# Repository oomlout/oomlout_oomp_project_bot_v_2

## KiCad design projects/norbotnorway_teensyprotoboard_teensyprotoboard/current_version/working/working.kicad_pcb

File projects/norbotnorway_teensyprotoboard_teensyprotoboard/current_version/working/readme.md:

# teensyprotoboard
 
## summary 
* id: norbotnorway_teensyprotoboard_teensyprotoboard
* user: norbotnorway
* name: teensyprotoboard
* board: teensyprotoboard
* repo: https://github.com/NorbotNorway/TeensyProtoboard
* src_file_repo_kicad_pcb: TeensyProtoboard.kicad_pcb
* src_file_repo_kicad_pcb_link: https://github.com/NorbotNorway/TeensyProtoboard/tree/master/TeensyProtoboard.kicad_pcb

* src_file_repo_sch: TeensyProtoboard.sch
* src_file_repo_sch_link: https://github.com/NorbotNorway/TeensyProtoboard/tree/master/TeensyProtoboard.sch
* full details link: https://github.com/oomlout/oomlout_oomp_project_bot_v_2/tree/main/projects/norbotnorway_teensyprotoboard_teensyprotoboard/current_version/working

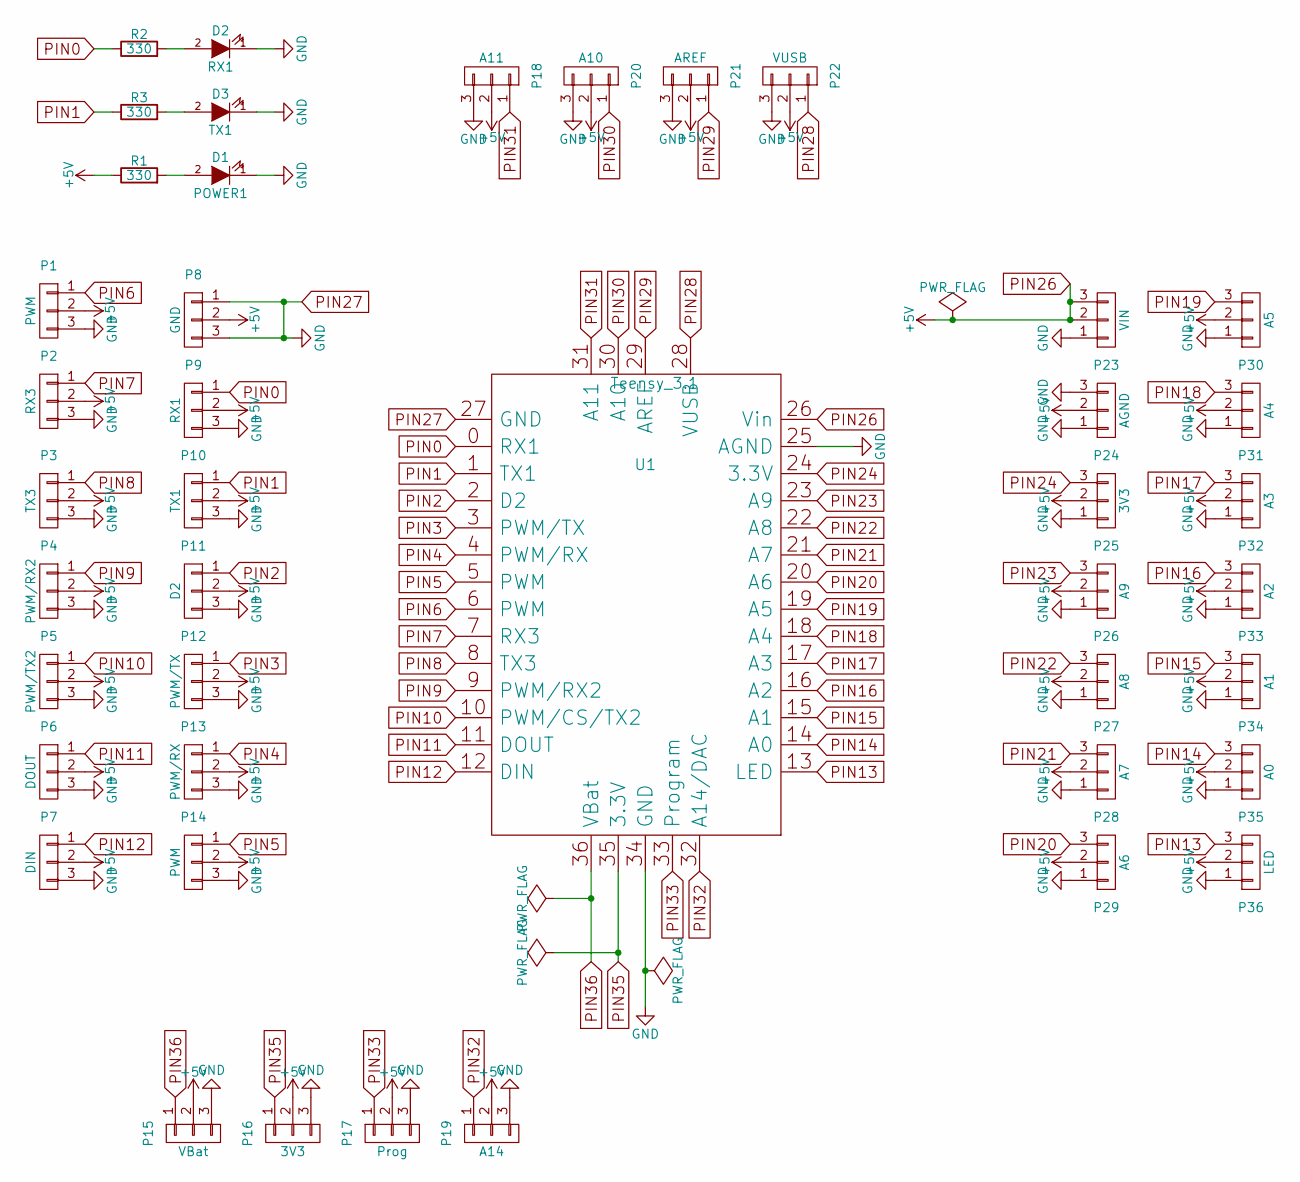
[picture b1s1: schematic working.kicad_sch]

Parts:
P1, P14: PWM; Pin_Header_Straight_1x03
P2: RX3; Pin_Header_Straight_1x03
P3: TX3; Pin_Header_Straight_1x03
P4: PWM/RX2; Pin_Header_Straight_1x03
P5: PWM/TX2; Pin_Header_Straight_1x03
P6: DOUT; Pin_Header_Straight_1x03
P7: DIN; Pin_Header_Straight_1x03
P8: GND; Pin_Header_Straight_1x03
P9: RX1; Pin_Header_Straight_1x03
P10: TX1; Pin_Header_Straight_1x03
P11: D2; Pin_Header_Straight_1x03
P12: PWM/TX; Pin_Header_Straight_1x03
P13: PWM/RX; Pin_Header_Straight_1x03
P15: VBat; Pin_Header_Straight_1x03
P16, P25: 3V3; Pin_Header_Straight_1x03
P17: Prog; Pin_Header_Straight_1x03
P18: A11; Pin_Header_Straight_1x03
P19: A14; Pin_Header_Straight_1x03
P20: A10; Pin_Header_Straight_1x03
P21: AREF; Pin_Header_Straight_1x03
P22: VUSB; Pin_Header_Straight_1x03
P23: VIN; Pin_Header_Straight_1x03
P24: AGND; Pin_Header_Straight_1x03
P26: A9; Pin_Header_Straight_1x03
P27: A8; Pin_Header_Straight_1x03
P28: A7; Pin_Header_Straight_1x03
P29: A6; Pin_Header_Straight_1x03
P30: A5; Pin_Header_Straight_1x03
P31: A4; Pin_Header_Straight_1x03
P32: A3; Pin_Header_Straight_1x03
P33: A2; Pin_Header_Straight_1x03
P34: A1; Pin_Header_Straight_1x03
P35: A0; Pin_Header_Straight_1x03
P36: LED; Pin_Header_Straight_1x03
POWER1: D1; SMB_Standard
R1, R2, R3: 330; R_0805_HandSoldering
RX1: D2; SMB_Standard
TX1: D3; SMB_Standard
U1: Teensy_3.1; Teensy-3.1_3.2

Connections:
unnamed: POWER1.2 (A), R1.2
unnamed: R2.2, RX1.2 (A)
unnamed: R3.2, TX1.2 (A)
PIN0: P9.1, R2.1, U1.0 (RX1)
PIN1: P10.1, R3.1, U1.1 (TX1)
PIN2: P11.1, U1.2 (D2)
PIN3: P12.1, U1.3 (PWM/TX)
PIN4: P13.1, U1.4 (PWM/RX)
PIN5: P14.1, U1.5 (PWM)
PIN6: P1.1, U1.6 (PWM)
PIN7: P2.1, U1.7 (RX3)
PIN8: P3.1, U1.8 (TX3)
PIN9: P4.1, U1.9 (PWM/RX2)
PIN10: P5.1, U1.10 (PWM/CS/TX2)
PIN11: P6.1, U1.11 (DOUT)
PIN12: P7.1, U1.12 (DIN)
PIN13: P36.3, U1.13 (LED)
PIN14: P35.3, U1.14 (A0)
PIN15: P34.3, U1.15 (A1)
PIN16: P33.3, U1.16 (A2)
PIN17: P32.3, U1.17 (A3)
PIN18: P31.3, U1.18 (A4)
PIN19: P30.3, U1.19 (A5)
PIN20: P29.3, U1.20 (A6)
PIN21: P28.3, U1.21 (A7)
PIN22: P27.3, U1.22 (A8)
PIN23: P26.3, U1.23 (A9)
PIN24: P25.3, U1.24 (3.3V)
PIN26: P1.2, P2.2, P3.2, P4.2, P5.2, P6.2, P7.2, P8.2, P9.2, P10.2, P11.2, P12.2, P13.2, P14.2, P15.2, P16.2, P17.2, P18.2, P19.2, P20.2, P21.2, P22.2, P23.2, P23.3, P24.2, P25.2, P26.2, P27.2, P28.2, P29.2, P30.2, P31.2, P32.2, P33.2, P34.2, P35.2, P36.2, R1.1, U1.26 (Vin)
PIN27: P1.3, P2.3, P3.3, P4.3, P5.3, P6.3, P7.3, P8.1, P8.3, P9.3, P10.3, P11.3, P12.3, P13.3, P14.3, P15.3, P16.3, P17.3, P18.3, P19.3, P20.3, P21.3, P22.3, P23.1, P24.1, P24.3, P25.1, P26.1, P27.1, P28.1, P29.1, P30.1, P31.1, P32.1, P33.1, P34.1, P35.1, P36.1, POWER1.1 (K), RX1.1 (K), TX1.1 (K), U1.25 (AGND), U1.27 (GND), U1.34 (GND)
PIN28: P22.1, U1.28 (VUSB)
PIN29: P21.1, U1.29 (AREF)
PIN30: P20.1, U1.30 (A10)
PIN31: P18.1, U1.31 (A11)
PIN32: P19.1, U1.32 (A14/DAC)
PIN33: P17.1, U1.33 (Program)
PIN35: P16.1, U1.35 (3.3V)
PIN36: P15.1, U1.36 (VBat)

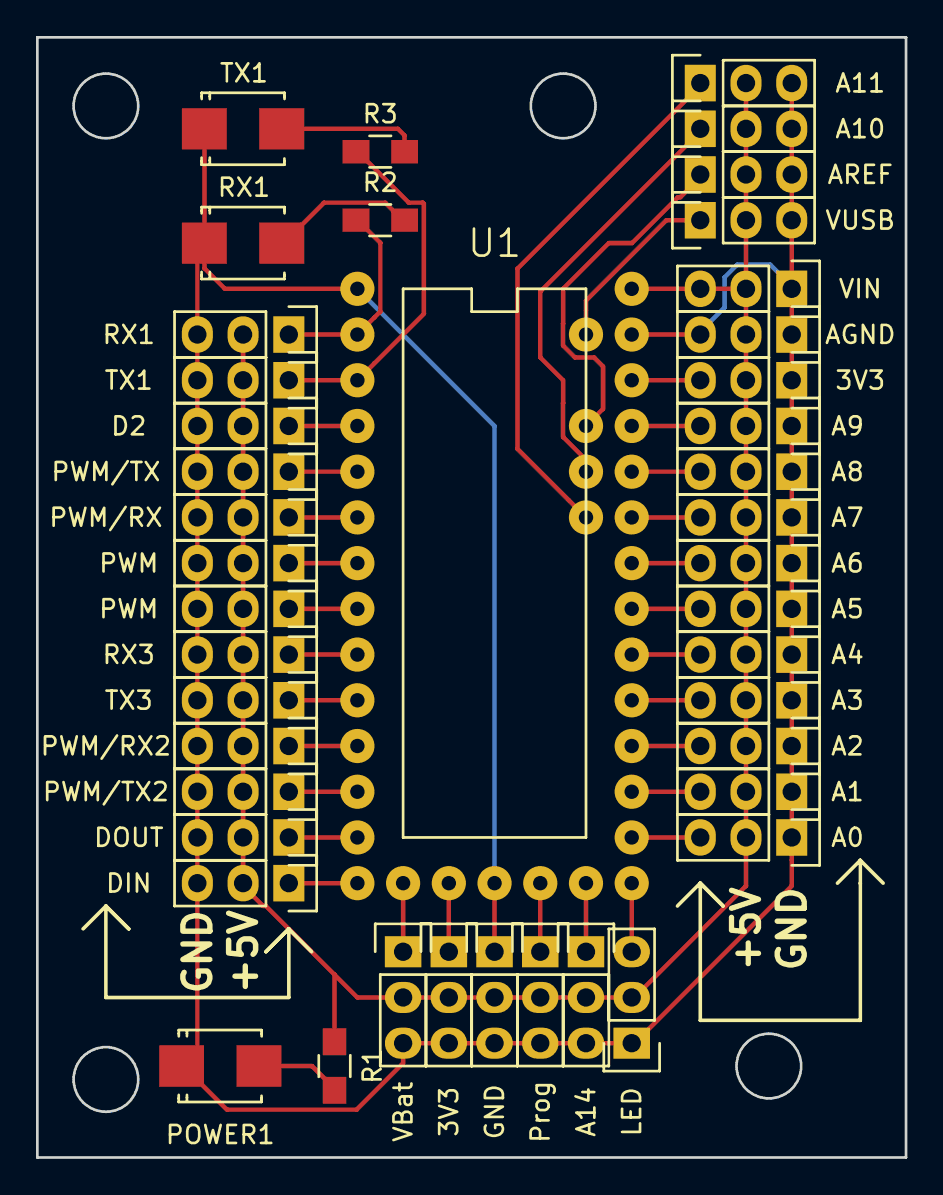
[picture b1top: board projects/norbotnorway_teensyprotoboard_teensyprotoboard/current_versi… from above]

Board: 2 copper layers, 48.3 x 62.2 mm, 43 parts (0 on the bottom side), 38 nets.

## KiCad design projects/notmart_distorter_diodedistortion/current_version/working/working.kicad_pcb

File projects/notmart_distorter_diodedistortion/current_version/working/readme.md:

# distorter
 
## summary 
* id: notmart_distorter_diodedistortion
* user: notmart
* name: distorter
* board: diodedistortion
* repo: https://github.com/notmart/distorter
* src_file_repo_kicad_pcb: diodedistortion.kicad_pcb
* src_file_repo_kicad_pcb_link: https://github.com/notmart/distorter/tree/master/diodedistortion.kicad_pcb

* src_file_repo_sch: diodedistortion.sch
* src_file_repo_sch_link: https://github.com/notmart/distorter/tree/master/diodedistortion.sch
* full details link: https://github.com/oomlout/oomlout_oomp_project_bot_v_2/tree/main/projects/notmart_distorter_diodedistortion/current_version/working

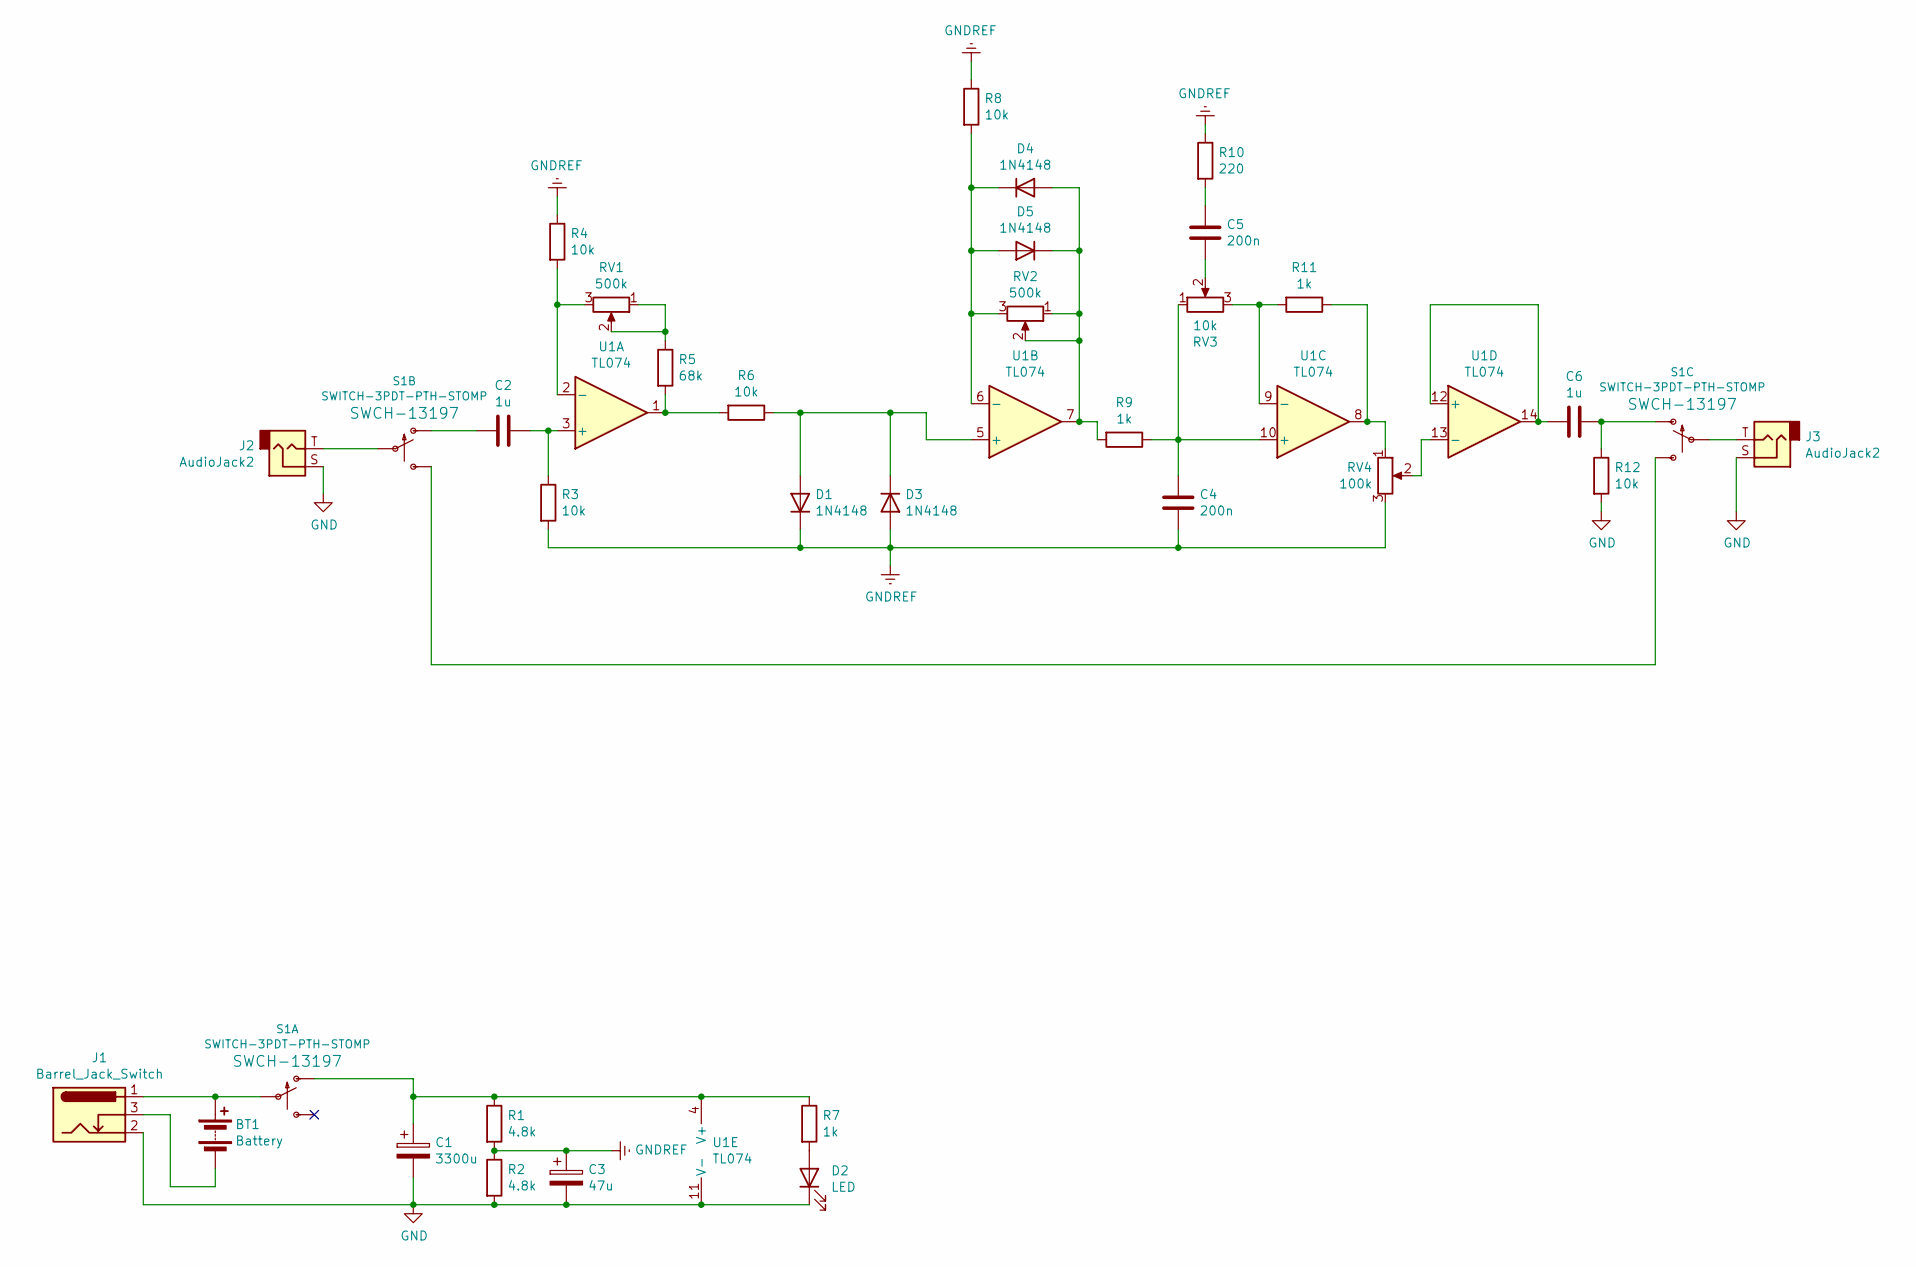
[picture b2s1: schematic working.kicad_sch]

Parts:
BT1: Battery; 1X02
C1: 3300u; CP_Radial_D13.0mm_P5.00mm
C2, C6: 1u; C_Rect_L7.2mm_W2.5mm_P5.00mm_FKS2_FKP2_MKS2_MKP2
C3: 47u; CP_Radial_D8.0mm_P5.00mm
C4, C5: 200n; C_Rect_L7.2mm_W2.5mm_P5.00mm_FKS2_FKP2_MKS2_MKP2
D1, D3, D4, D5: 1N4148; D_DO-35_SOD27_P7.62mm_Horizontal
D2: LED; LED_D3.0mm
J1: Barrel_Jack_Switch; BarrelJack_Horizontal
J2, J3: AudioJack2; Jack 6.35mm PJ603
R1, R2: 4.8k; R_Axial_DIN0204_L3.6mm_D1.6mm_P7.62mm_Horizontal
R3, R4, R6, R8, R12: 10k; R_Axial_DIN0204_L3.6mm_D1.6mm_P7.62mm_Horizontal
R5: 68k; R_Axial_DIN0204_L3.6mm_D1.6mm_P7.62mm_Horizontal
R7, R9, R11: 1k; R_Axial_DIN0204_L3.6mm_D1.6mm_P7.62mm_Horizontal
R10: 220; R_Axial_DIN0204_L3.6mm_D1.6mm_P7.62mm_Horizontal
RV1, RV2: 500k; Potentiometer_Alps_RK09K_Single_Vertical
RV3: 10k; Potentiometer_Alps_RK09K_Single_Vertical
RV4: 100k; Potentiometer_Bourns_3386P_Vertical
S1: SWITCH-3PDT-PTH-STOMP; 3PDT_Small
U1: TL074; DIP-14_W7.62mm_Socket_LongPads

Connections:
GND: C1.2, C3.2, D2.1 (K), J1.2, J2.S, J3.S, R2.2, R12.2, U1.11 (V-)
GNDREF: C3.1, C4.2, D1.1 (K), D3.2 (A), R1.2, R2.1, R3.2, R4.1, R8.1, R10.1, RV4.3
unnamed: BT1.1 (+), J1.1, S1.P$2
unnamed: BT1.2 (-), J1.3
unnamed: C1.1, R1.1, R7.1, S1.P$1 (O), U1.4 (V+)
unnamed: C2.1, R3.1, U1.3 (+)
unnamed: C2.2, S1.P$4 (O)
unnamed: C4.1, R9.1, RV3.1, U1.10 (+)
unnamed: C5.1, R10.2
unnamed: C5.2, RV3.2
unnamed: C6.1, R12.1, S1.P$7 (O)
unnamed: C6.2, U1.12 (+), U1.14
unnamed: D1.2 (A), D3.1 (K), R6.1, U1.5 (+)
unnamed: D2.2 (A), R7.2
unnamed: D4.1 (K), D5.2 (A), R8.2, RV2.3, U1.6 (-)
unnamed: D4.2 (A), D5.1 (K), R9.2, RV2.1, RV2.2, U1.7
unnamed: J2.T, S1.P$5
unnamed: J3.T, S1.P$8
unnamed: R4.2, RV1.3, U1.2 (-)
unnamed: R5.1, RV1.1, RV1.2
unnamed: R5.2, R6.2, U1.1
unnamed: R11.1, RV4.1, U1.8
unnamed: R11.2, RV3.3, U1.9 (-)
unnamed: RV4.2, U1.13 (-)
unnamed: S1.P$6 (S), S1.P$9 (S)

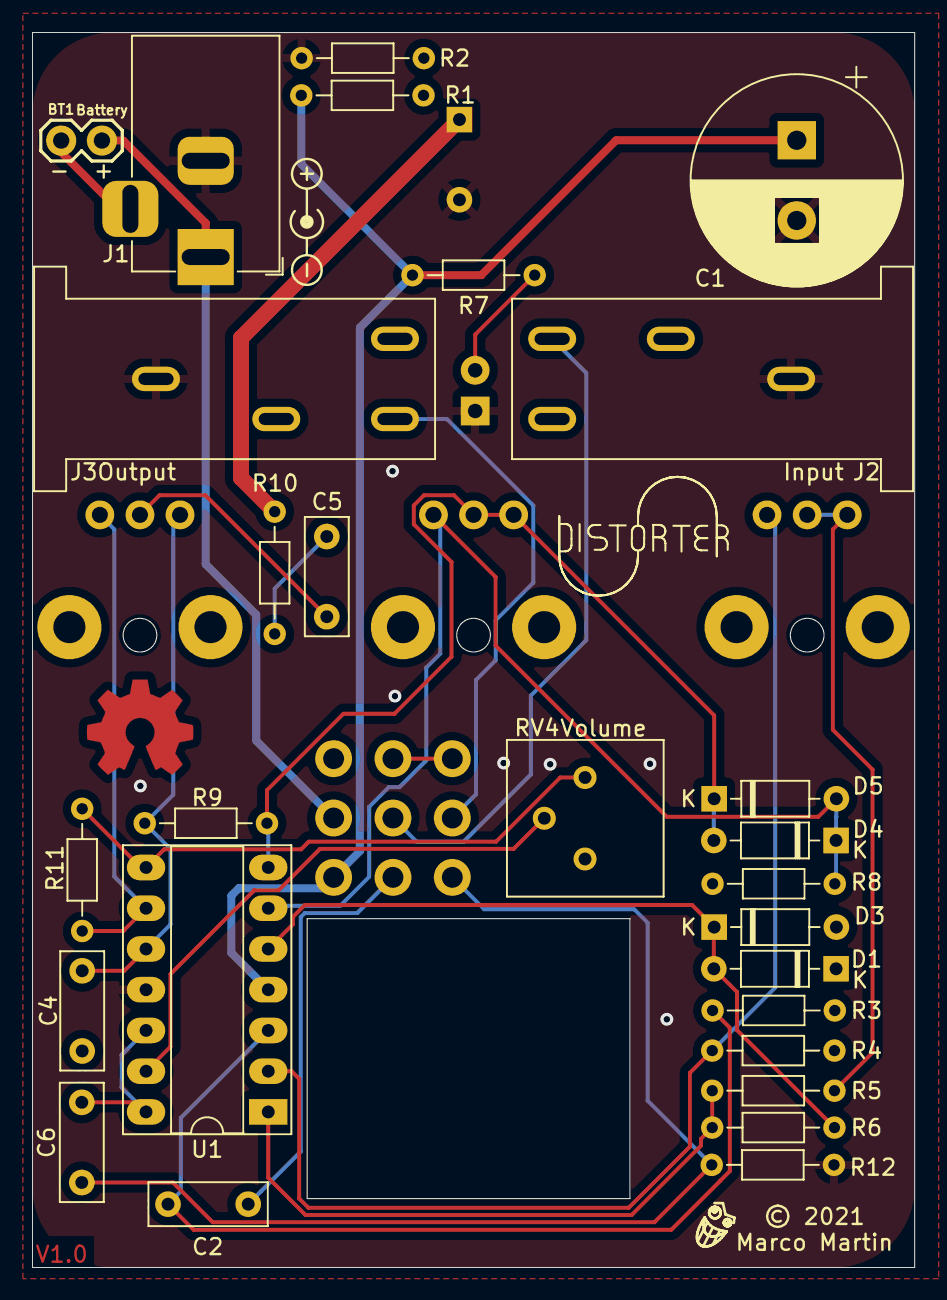
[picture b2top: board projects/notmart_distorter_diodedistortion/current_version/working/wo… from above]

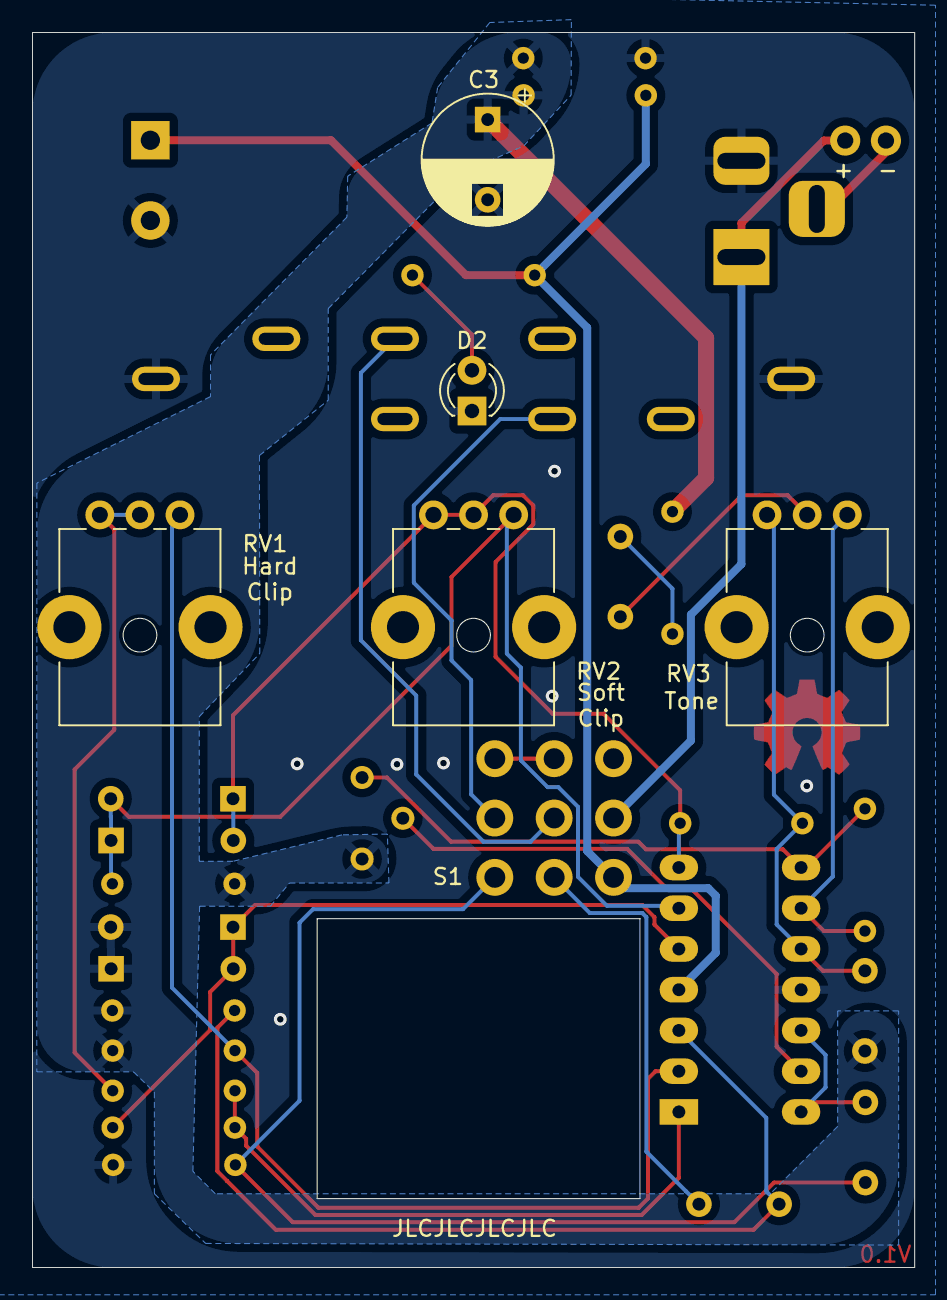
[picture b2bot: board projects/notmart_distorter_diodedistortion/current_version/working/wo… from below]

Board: 2 copper layers, 55.0 x 77.0 mm, 33 parts (6 on the bottom side), 25 nets.

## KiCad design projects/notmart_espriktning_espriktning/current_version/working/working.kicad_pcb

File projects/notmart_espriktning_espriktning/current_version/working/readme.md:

# espriktning
 
## summary 
* id: notmart_espriktning_espriktning
* user: notmart
* name: espriktning
* board: espriktning
* repo: https://github.com/notmart/espriktning
* src_file_repo_kicad_pcb: espriktning.kicad_pcb
* src_file_repo_kicad_pcb_link: https://github.com/notmart/espriktning/tree/master/espriktning.kicad_pcb
* src_file_repo_kicad_sch: espriktning (phobos's conflicted copy 2022-04-14).kicad_sch
* src_file_repo_kicad_sch_link: https://github.com/notmart/espriktning/tree/master/espriktning (phobos's conflicted copy 2022-04-14).kicad_sch

* src_file_repo_sch: espriktning.sch
* src_file_repo_sch_link: https://github.com/notmart/espriktning/tree/master/espriktning.sch
* full details link: https://github.com/oomlout/oomlout_oomp_project_bot_v_2/tree/main/projects/notmart_espriktning_espriktning/current_version/working

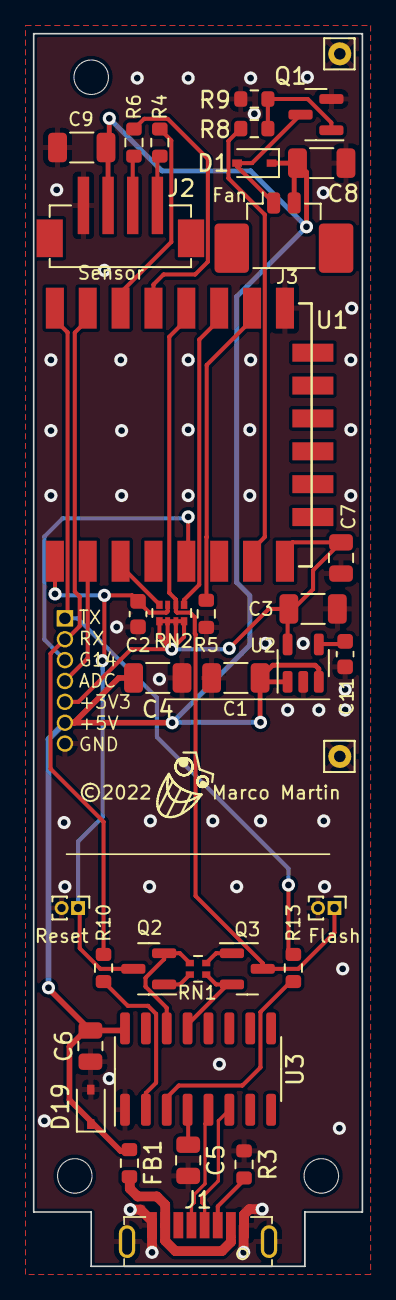
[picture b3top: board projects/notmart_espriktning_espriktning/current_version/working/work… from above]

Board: 2 copper layers, 20.0 x 75.0 mm, 37 parts (0 on the bottom side), 31 nets.

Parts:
C1, C3, C4, C8, C9: 10u; C_1206_3216Metric
C2, C11: 470p; C_0603_1608Metric
C5, C6: 100n; C_0805_2012Metric
C7: 100u; C_0805_2012Metric
D1, D19: 1N4007; D_SOD-323
FB1: 60R; R_0603_1608Metric
J1: USB_C_Receptacle_USB2.0; usb-c-vertical-8
J2: Conn_Sensor; X1502WVS-04-9TSN
J3: Conn_Fan; Molex_PicoBlade_53398-0271_1x02-1MP_P1.25mm_Vertical
J4: Conn_01x08; PinSocket_1x07_P1.27mm_Vertical
J6, J7: Conn_01x01_Male; Pin_D0.7mm_L6.5mm_W1.8mm_FlatFork
Q1: 2N7002K; SOT-23
Q2, Q3: S8050; SOT-23
R3: 5.1k; R_0603_1608Metric
R4, R6, R10, R13: 470R; R_0603_1608Metric
R5, R9: 12k; R_0603_1608Metric
R8: 100; R_0603_1608Metric
RN1: 10k; R_Array_Convex_2x0402
RN2: 12k; R_Array_Convex_4x0402
SW1: Reset; PinHeader_1x02_P1.00mm_Vertical
SW2: Flash; PinHeader_1x02_P1.00mm_Vertical
U1: ESP-12F; ESP-12E_SMD
U2: SPX3819M5-L-3-3_SOT-23-5; SOT-23-5
U3: CH340C; SOIC-16_3.9x9.9mm_P1.27mm

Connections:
+3V3: C3.1, C7.1, J4.5, RN2.5 (R4.2), RN2.6 (R3.2), RN2.7 (R2.2), RN2.8 (R1.2), U1.8 (VCC), U2.5 (OUT)
+5V: C1.1, C4.1, C6.1, C8.1, C9.1, D1.1 (K), D19.1 (K), FB1.2, J2.2, J3.2, J4.6, U2.1 (IN), U2.3 (EN), U3.16 (VCC)
/D_N: J1.B7 (D-), U3.6 (UD-)
/D_P: J1.B6 (D+), U3.5 (UD+)
/VBUS: FB1.1, J1.A4 (VBUS)
ADC: J4.4, U1.2 (ADC)
GND: C1.2, C2.2, C3.2, C4.2, C5.2, C6.2, C7.2, C8.2, C9.2, C11.2, D19.2 (A), J1.A1 (GND), J1.S1 (SHIELD), J2.1, J4.7, J6.1, J7.1, Q1.2 (S), R3.1, R5.2, R9.2, SW1.2, SW2.2, U1.9 (GND), U2.2 (GND), U3.1 (GND)
GPIO0: Q3.3 (C), RN2.2 (R2.1), SW2.1, U1.12 (GPIO0)
GPIO2: RN2.1 (R1.1), U1.11 (GPIO2)
GPIO4: R6.2, U1.13 (GPIO4)
GPIO5: R4.2, U1.14 (GPIO5)
GPIO13: R8.2, U1.7 (GPIO13)
GPIO14: J4.3, U1.5 (GPIO14)
GPIO15: R5.1, U1.10 (GPIO15)
unnamed: C5.1, U3.4 (V3)
unnamed: C11.1, U2.4 (BP)
unnamed: D1.2 (A), J3.1, Q1.3 (D)
unnamed: J1.A5 (CC1), R3.2
unnamed: J2.3, R6.1
unnamed: J2.4, R4.1
unnamed: Q1.1 (G), R8.1, R9.1
unnamed: Q2.1 (B), RN1.2 (R1.2)
unnamed: Q2.2 (E), RN1.4 (R2.2), U3.14 (~RTS)
unnamed: Q3.1 (B), RN1.3 (R2.1)
unnamed: Q3.2 (E), RN1.1 (R1.1), U3.13 (~DTR)
unnamed: R10.2, U3.2 (TXD)
unnamed: R13.2, U3.3 (RXD)
unnamed: RN2.4 (R4.1), U1.3 (CH_PD)
RST: C2.1, Q2.3 (C), RN2.3 (R3.1), SW1.1, U1.1 (REST)
RX: J4.2, R10.1, U1.15 (RXD)
TX: J4.1, R13.1, U1.16 (TXD)

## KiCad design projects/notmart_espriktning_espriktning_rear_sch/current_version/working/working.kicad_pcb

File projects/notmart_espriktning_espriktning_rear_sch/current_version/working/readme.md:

# espriktning
 
## summary 
* id: notmart_espriktning_espriktning_rear_sch
* user: notmart
* name: espriktning
* board: espriktning_rear_sch
* repo: https://github.com/notmart/espriktning
* src_file_repo_kicad_pcb: rear/espriktning-rear.sch.kicad_pcb
* src_file_repo_kicad_pcb_link: https://github.com/notmart/espriktning/tree/master/rear/espriktning-rear.sch.kicad_pcb
* src_file_repo_kicad_sch: rear/espriktning (phobos's conflicted copy 2022-04-14).kicad_sch
* src_file_repo_kicad_sch_link: https://github.com/notmart/espriktning/tree/master/rear/espriktning (phobos's conflicted copy 2022-04-14).kicad_sch

* src_file_repo_sch: rear/espriktning-rear.sch.sch
* src_file_repo_sch_link: https://github.com/notmart/espriktning/tree/master/rear/espriktning-rear.sch.sch
* full details link: https://github.com/oomlout/oomlout_oomp_project_bot_v_2/tree/main/projects/notmart_espriktning_espriktning_rear_sch/current_version/working

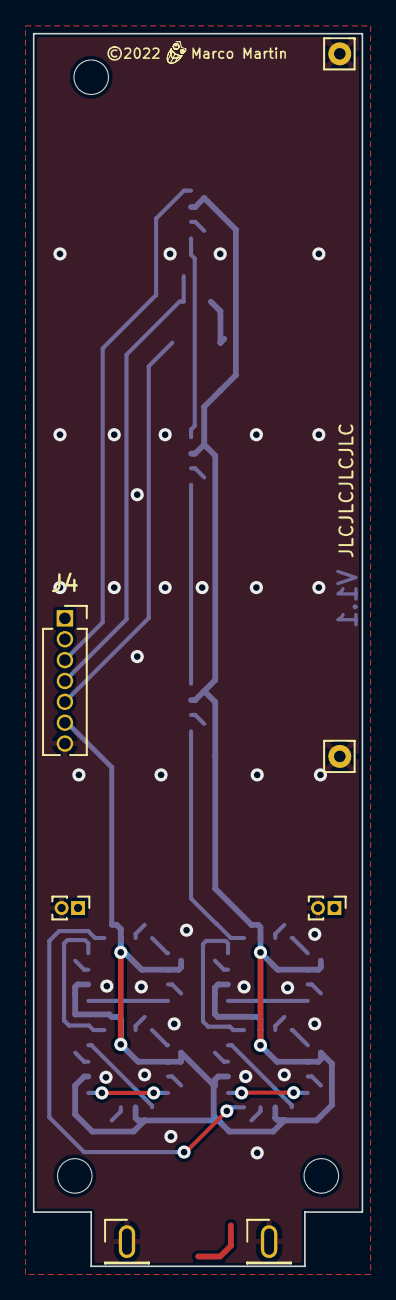
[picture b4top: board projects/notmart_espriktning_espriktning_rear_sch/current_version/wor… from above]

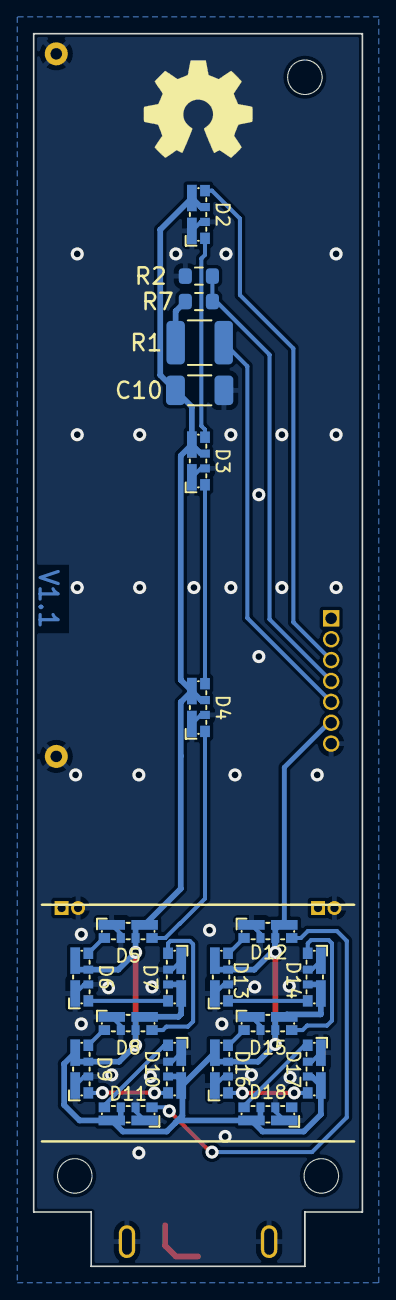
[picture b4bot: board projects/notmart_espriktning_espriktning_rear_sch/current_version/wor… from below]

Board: 2 copper layers, 20.0 x 75.0 mm, 26 parts (21 on the bottom side), 22 nets.

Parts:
C10: 10u; C_1206_3216Metric
D2, D3, D4, D5, D6, D7, D8, D9, D10, D11, D12, D13, D14, D15, D16, D17, D18: SK6812; SK6812D-EC3210R
J2, J3: Conn_01x01_Male; Pin_D0.7mm_L6.5mm_W1.8mm_FlatFork
J4: Conn_01x08; PinSocket_1x07_P1.27mm_Vertical
R1: GT36528; R_1210_3225Metric
R2, R7: 12k; R_0603_1608Metric
SW1: Reset; PinHeader_1x02_P1.00mm_Vertical
SW2: Flash; PinHeader_1x02_P1.00mm_Vertical

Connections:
+3V3: J4.5, R1.1
+5V: C10.1, D2.3 (VDD), D3.3 (VDD), D4.3 (VDD), D5.3 (VDD), D6.3 (VDD), D7.3 (VDD), D8.3 (VDD), D9.3 (VDD), D10.3 (VDD), D11.3 (VDD), D12.3 (VDD), D13.3 (VDD), D14.3 (VDD), D15.3 (VDD), D16.3 (VDD), D17.3 (VDD), D18.3 (VDD), J4.6
ADC: J4.4, R2.1, R7.2
GND: C10.2, D2.1 (VSS), D3.1 (VSS), D4.1 (VSS), D5.1 (VSS), D6.1 (VSS), D7.1 (VSS), D8.1 (VSS), D9.1 (VSS), D10.1 (VSS), D11.1 (VSS), D12.1 (VSS), D13.1 (VSS), D14.1 (VSS), D15.1 (VSS), D16.1 (VSS), D17.1 (VSS), D18.1 (VSS), J2.1, J3.1, J4.7, R2.2, SW1.2, SW2.2
GPIO14: D2.2 (DIN), J4.3
unnamed: D2.4 (DOUT), D3.2 (DIN)
unnamed: D3.4 (DOUT), D4.2 (DIN)
unnamed: D4.4 (DOUT), D5.2 (DIN)
unnamed: D5.4 (DOUT), D6.2 (DIN)
unnamed: D6.4 (DOUT), D7.2 (DIN)
unnamed: D7.4 (DOUT), D8.2 (DIN)
unnamed: D8.4 (DOUT), D9.2 (DIN)
unnamed: D9.4 (DOUT), D10.2 (DIN)
unnamed: D10.4 (DOUT), D11.2 (DIN)
unnamed: D11.4 (DOUT), D12.2 (DIN)
unnamed: D12.4 (DOUT), D13.2 (DIN)
unnamed: D13.4 (DOUT), D14.2 (DIN)
unnamed: D14.4 (DOUT), D15.2 (DIN)
unnamed: D15.4 (DOUT), D16.2 (DIN)
unnamed: D16.4 (DOUT), D17.2 (DIN)
unnamed: D17.4 (DOUT), D18.2 (DIN)
unnamed: R1.2, R7.1

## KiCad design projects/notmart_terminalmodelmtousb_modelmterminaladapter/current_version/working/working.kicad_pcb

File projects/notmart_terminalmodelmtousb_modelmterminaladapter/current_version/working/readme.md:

# terminalmodelmtousb
 
## summary 
* id: notmart_terminalmodelmtousb_modelmterminaladapter
* user: notmart
* name: terminalmodelmtousb
* board: modelmterminaladapter
* repo: https://github.com/notmart/terminalmodelmtousb
* src_file_repo_kicad_pcb: kicad/modelMterminalAdapter.kicad_pcb
* src_file_repo_kicad_pcb_link: https://github.com/notmart/terminalmodelmtousb/tree/main/kicad/modelMterminalAdapter.kicad_pcb

* src_file_repo_sch: kicad/modelMterminalAdapter.sch
* src_file_repo_sch_link: https://github.com/notmart/terminalmodelmtousb/tree/main/kicad/modelMterminalAdapter.sch
* full details link: https://github.com/oomlout/oomlout_oomp_project_bot_v_2/tree/main/projects/notmart_terminalmodelmtousb_modelmterminaladapter/current_version/working

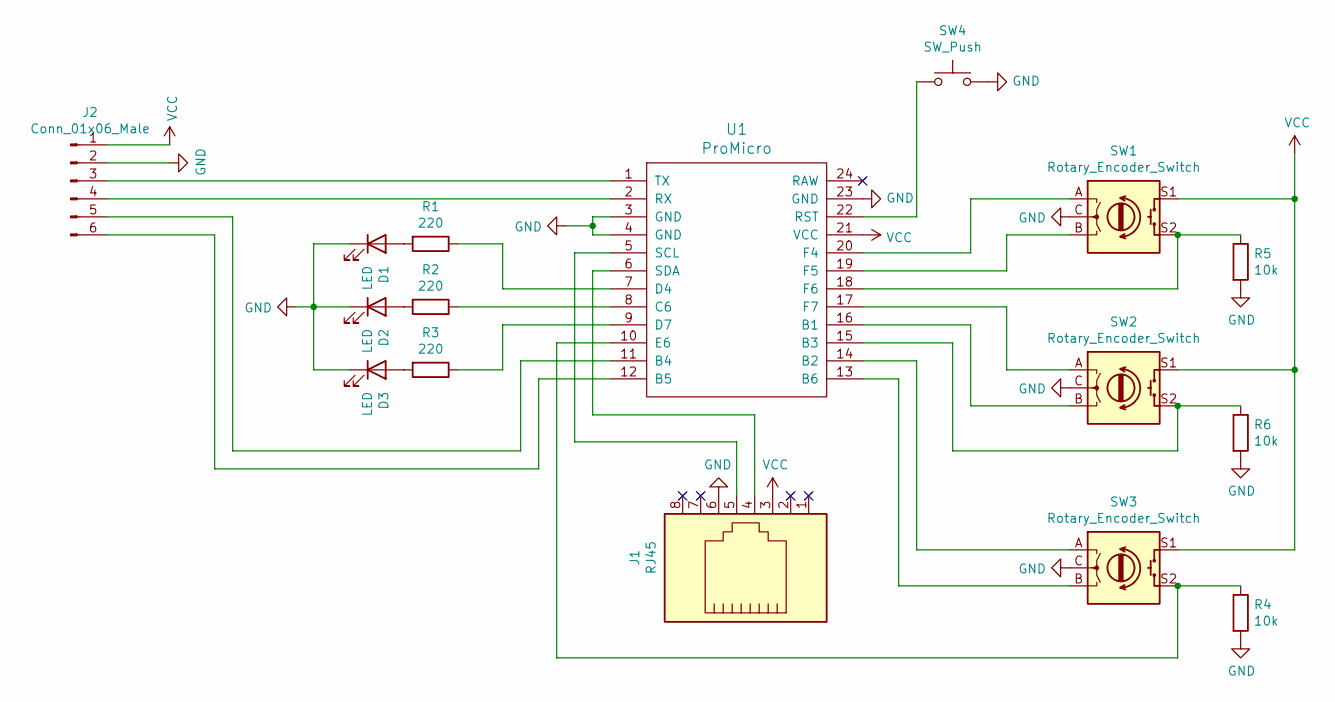
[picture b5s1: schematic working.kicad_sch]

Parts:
D1, D2, D3: LED; LED_D5.0mm
J1: RJ45; RJ45_Amphenol_RJHSE5380
J2: Conn_01x06_Male; PinHeader_1x06_P2.54mm_Vertical
R1, R2, R3: 220; R_Axial_DIN0207_L6.3mm_D2.5mm_P7.62mm_Horizontal
R4, R5, R6: 10k; R_Axial_DIN0207_L6.3mm_D2.5mm_P7.62mm_Horizontal
SW1, SW2, SW3: Rotary_Encoder_Switch; RotaryEncoder_Alps_EC11E-Switch_Vertical_H20mm
SW4: SW_Push; SW_SPST_CK_RS282G05A3
U1: ProMicro

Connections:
GND: D1.1 (K), D2.1 (K), D3.1 (K), J1.6, J2.2, R4.2, R5.2, R6.2, SW1.C, SW2.C, SW3.C, SW4.2, U1.3 (GND), U1.4 (GND), U1.23 (GND)
unnamed: D1.2 (A), R1.2
unnamed: D2.2 (A), R2.2
unnamed: D3.2 (A), R3.2
unnamed: J1.4, U1.6 (SDA)
unnamed: J1.5, U1.5 (SCL)
unnamed: J2.3, U1.1 (TX)
unnamed: J2.4, U1.2 (RX)
unnamed: J2.5, U1.11 (B4)
unnamed: J2.6, U1.12 (B5)
unnamed: R1.1, U1.7 (D4)
unnamed: R2.1, U1.8 (C6)
unnamed: R3.1, U1.9 (D7)
unnamed: R4.1, SW3.S2, U1.10 (E6)
unnamed: R5.1, SW1.S2, U1.18 (F6)
unnamed: R6.1, SW2.S2, U1.15 (B3)
unnamed: SW1.A, U1.20 (F4)
unnamed: SW1.B, U1.19 (F5)
unnamed: SW2.A, U1.17 (F7)
unnamed: SW2.B, U1.16 (B1)
unnamed: SW3.A, U1.14 (B2)
unnamed: SW3.B, U1.13 (B6)
unnamed: SW4.1, U1.22 (RST)
VCC: J1.3, J2.1, SW1.S1, SW2.S1, SW3.S1, U1.21 (VCC)

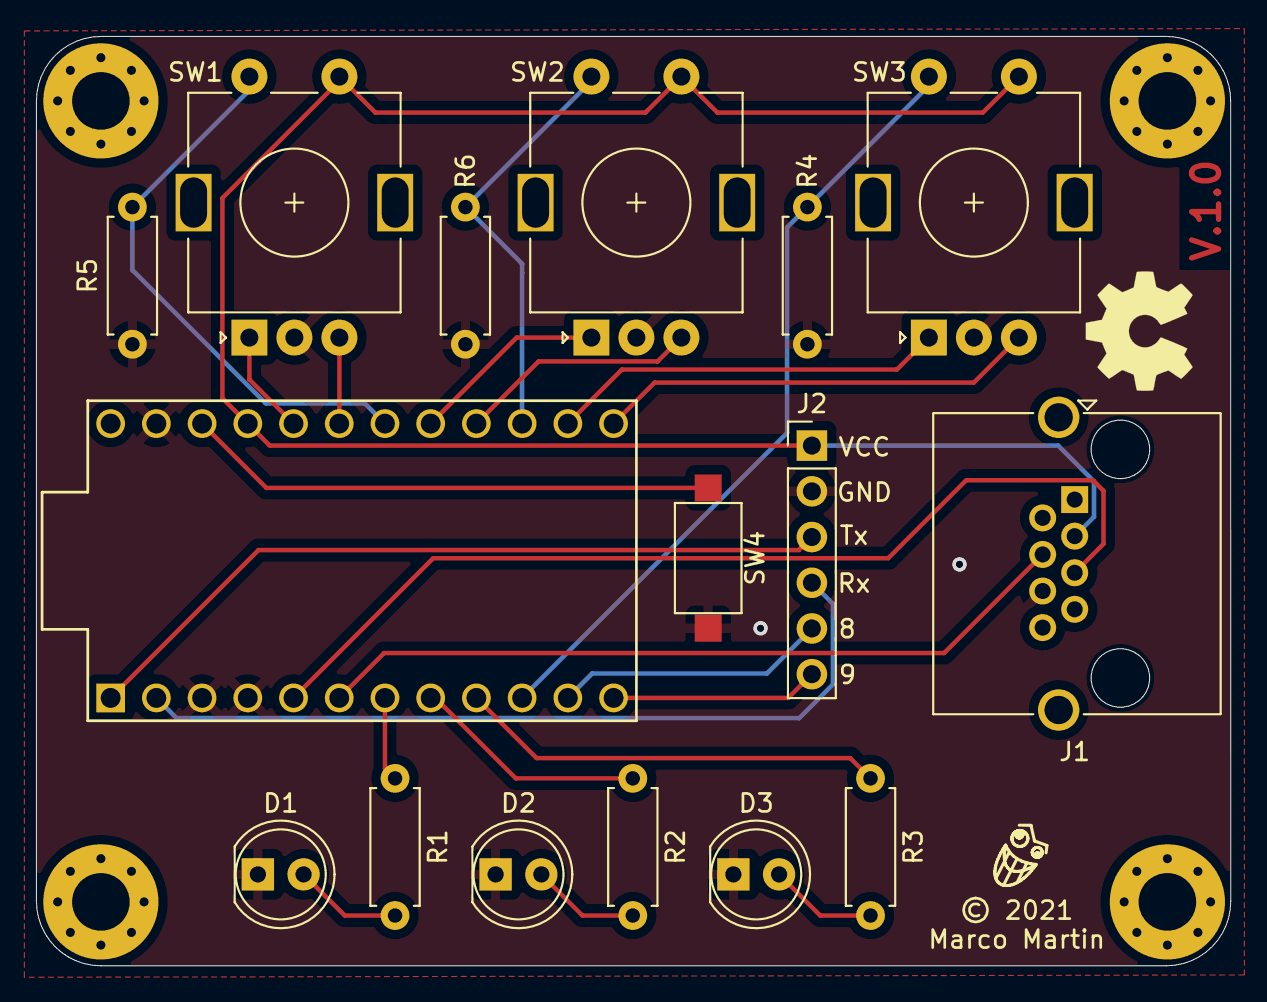
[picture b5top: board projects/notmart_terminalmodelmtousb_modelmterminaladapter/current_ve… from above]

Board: 2 copper layers, 66.3 x 51.6 mm, 20 parts (0 on the bottom side), 24 nets.

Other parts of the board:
mount1, mount2, mount3, mount4: MountingHole_3.2mm_M3_Pad_Via

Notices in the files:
projects/notmart_distorter_diodedistortion/current_version/working/working.kicad_pcb:
© 2021
projects/notmart_espriktning_espriktning/current_version/working/working.kicad_pcb:
©2022 Marco Martin
projects/notmart_theresynth_theresynth/current_version/working/working.kicad_pcb:
Theresynth © 2020 Marco Martin
